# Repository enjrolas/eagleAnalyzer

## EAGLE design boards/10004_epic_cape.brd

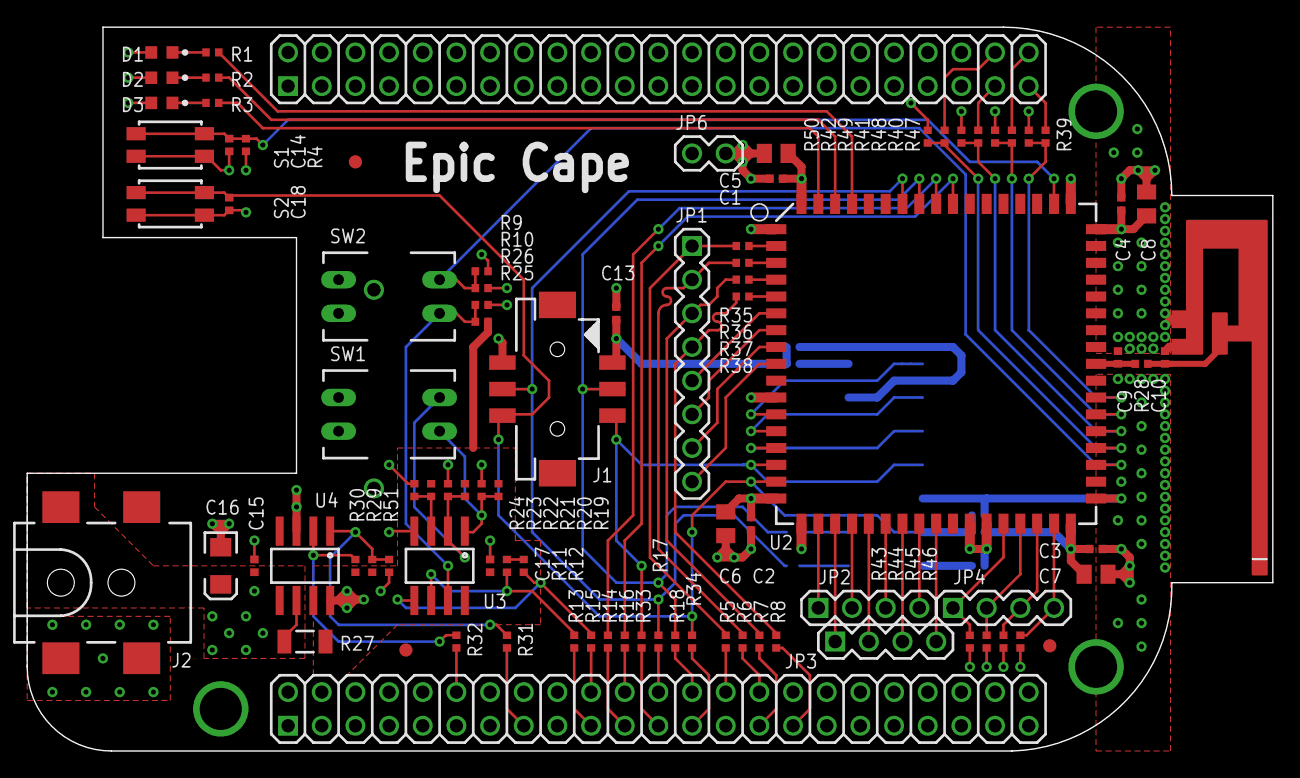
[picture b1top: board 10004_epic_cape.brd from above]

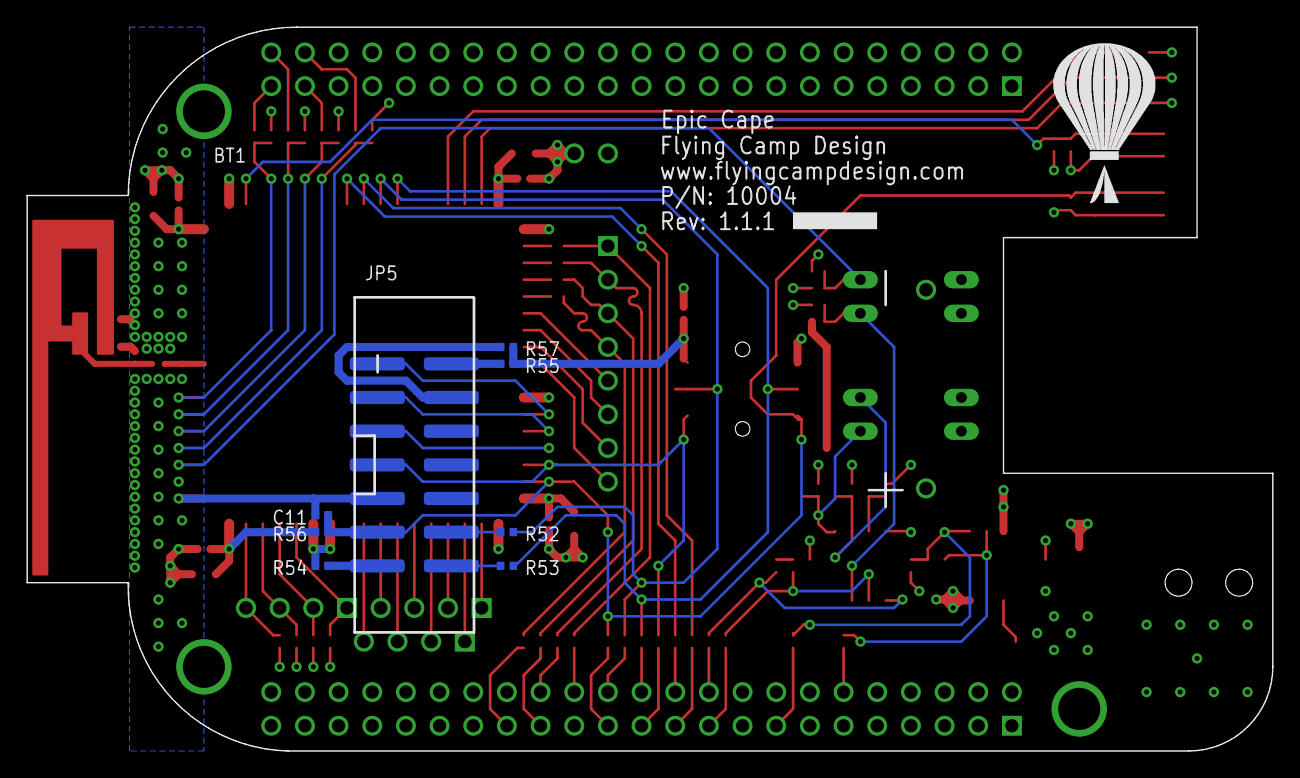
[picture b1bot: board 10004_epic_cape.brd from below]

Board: 4 copper layers, 94.0 x 54.6 mm, 99 parts (10 on the bottom side), 83 nets.

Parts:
ANT1: 2.4GHZ_INVERTED_F_ANTENNA
BT1: KEYSTONE_2462
C1, C2, C3, C4, C13, C14, C15, C17: 0.1u; CAPC1005
C5, C6, C7, C8: CAPC2012
C9, C10, C11, C18: CAPC1005
C16: 47u; EIA3216
D1: RED; LEDC1608
D2: GREEN; LEDC1608
D3: YELLOW; LEDC1608
J1: MSP430_BSL_HDR/SMD; HIROSE_DF11G-XXDP-2V
J2: 5.5x2.1mm Barrel; POWER_JACK_SMD
JP1: 1X08
JP2, JP3, JP4: 1X04
JP5: M07X2SHD_SMD; 2X7-SHROUDED_SMD
JP6: M02PTH; 1X02
R1, R2, R3: 470; RESC1005
R4, R29, R30, R43, R44, R45, R46, R47, R48, R49, R50, R51: 10K; RESC1005
R5, R6, R7, R8, R13, R14, R15, R16, R17, R18, R28, R31, R32, R33, R34, R35, R36, R37, R38, R39, R40, R41, R42, R52, R53, R54, R55, R57: 0; RESC1005
R9, R10, R19, R20, R21, R22, R23, R24, R25, R26: 100K; RESC1005
R11, R12: 5.6K; RESC1005
R27: 0; RESC3216
R56: RESC1005
S1, S2: PANASONIC_EVQP2
SW1, SW2: KAS1102ET; DIPSWITCH-02
U1: BEAGLEBONE_OUTLINE; BEAGLEBONE_SHIELD
U2: EPIC-CORE_A; EPIC_LCC68
U3: CAT24C256/SOIC-8; SOIC-8
U4: MIC2025/SOIC-8; SOIC-8
U$2: LOGO
U$3, U$4, U$5: FIDUCIAL1X2.5; FIDUCIAL-1X2.5

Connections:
3V3: BT1.+, C1.1, C2.1, C3.2, C4.2, C5.1, C6.1, C7.2, C8.2, C13.1, C15.1, C16.A, D1.A, D2.A, D3.A, J1.P$1, J2.VIN0, JP6.1, R4.2, R9.2, R27.1, R43.2, R44.2, R45.2, R46.2, R47.2, R48.2, R49.2, R50.2, R55.2, R56.2, R57.2, U2.P$17, U2.P$34, U2.P$51, U2.P$68, U4.6, U4.8
BB_GPIO1_16: R31.2, U1.61
BB_GPIO1_17: R33.2, U1.69
BB_GPIO1_28: R32.2, U1.58
BB_GPIO2_6: R39.2, U1.45
BB_GPIO2_7: R40.2, U1.46
BB_GPIO2_8: R41.2, U1.43
BB_GPIO2_9: R42.2, U1.44
BB_GPIO3_21: R34.2, U1.71
BB_I2C2_SCL: R11.1, R13.1, U3.6
BB_I2C2_SCL_ST: R13.2, U1.65
BB_I2C2_SDA: R12.1, R15.1, U3.5
BB_I2C2_SDA_ST: R15.2, U1.66
BB_SPI1_CS0: R5.2, U1.74
BB_SPI1_DI: R6.2, U1.76
BB_SPI1_DO: R7.2, U1.75
BB_SPI1_SCLK: R8.2, U1.77
BB_UART1_RXD: R18.2, U1.72
BB_UART1_TXD: R17.2, U1.70
BB_UART2_RXD: R16.2, U1.68
BB_UART2_TXD: R14.2, U1.67
CAPE_EEPROM_A0: R19.1, R20.2, SW1.1, U3.1
CAPE_EEPROM_A1: R21.1, R22.2, SW1.2, U3.2
CAPE_EEPROM_A2: R23.1, R24.2, U3.3
CAPE_EEPROM_WP: R25.1, R26.2, SW2.1, U3.7
EPIC_ADC0: JP2.1, U2.P$19
EPIC_ADC1: JP3.1, U2.P$20
EPIC_ADC2: JP2.2, U2.P$21
EPIC_ADC3: JP3.2, U2.P$22
EPIC_ADC4: JP2.3, U2.P$23
EPIC_ADC5: JP3.3, U2.P$24
EPIC_ADC6: JP2.4, U2.P$25
EPIC_ADC7: JP3.4, U2.P$26
EPIC_FLASH_WP: R9.1, R10.2, SW2.2, U2.P$37
EPIC_LED1: R1.2, U2.P$65
EPIC_LED2: R2.2, U2.P$66
EPIC_LED3: R3.2, U2.P$67
EPIC_MISO1: JP1.3, R7.1, R37.1
EPIC_MISO1_ST: R37.2, U2.P$4
EPIC_MOSI1: JP1.2, R6.1, R36.1
EPIC_MOSI1_ST: R36.2, U2.P$3
EPIC_P1.2: JP4.1, R43.1, U2.P$30
EPIC_P1.5: JP4.2, R44.1, U2.P$31
EPIC_P1.6: JP4.3, R45.1, U2.P$32
EPIC_P1.7: JP4.4, R46.1, U2.P$33
EPIC_P2.0: R42.1, R50.1, U2.P$38
EPIC_P2.1: R41.1, R49.1, U2.P$39
EPIC_P2.3: R40.1, R48.1, U2.P$40
EPIC_P2.6: R39.1, R47.1, U2.P$41
EPIC_P5.4: JP1.5, U2.P$6
EPIC_P5.5: JP1.6, U2.P$7
EPIC_P5.6: JP1.7, U2.P$8
EPIC_P5.7: JP1.8, U2.P$9
EPIC_RFOUT: C9.1, R28.1, U2.P$43
EPIC_RST/NMI: C11.1, C18.1, J1.P$6, JP5.11, R34.1, R56.1, S2.P$1, S2.P$3, U2.P$16
EPIC_SCLK1: JP1.4, R8.1, R38.1
EPIC_SCLK1_ST: R38.2, U2.P$5
EPIC_STE1: JP1.1, R5.1, R35.1
EPIC_STE1_ST: R35.2, U2.P$2
EPIC_TCK: J1.P$5, JP5.7, R33.1, U2.P$15
EPIC_TDI/TCLK: JP5.3, U2.P$13
EPIC_TDO/TDI: JP5.1, U2.P$12
EPIC_TMS: JP5.5, U2.P$14
EPIC_UART0RX: R14.1, U2.P$60
EPIC_UART0TX: R16.1, U2.P$59
EPIC_UART1RX: J1.P$4, R17.1, R53.2, U2.P$62
EPIC_UART1TX: J1.P$3, R18.1, R52.2, U2.P$61
EPIC_USER_INT: C14.1, R4.1, S1.P$1, S1.P$3, U2.P$53
FEED: ANT1.FEED, C10.1, R28.2
GND: BT1.-, C1.2, C2.2, C3.1, C4.1, C5.2, C6.2, C7.1, C8.1, C11.2, C13.2, C14.2, C15.2, C16.C, C17.2, C18.2, J1.P$2, J2.GND, J2.P$4, JP5.9, JP6.2, R10.1, R20.1, R22.1, R24.1, R26.1, R51.1, R54.1, S1.P$2, S1.P$4, S2.P$2, S2.P$4, SW1.3, SW1.4, SW2.3, SW2.4, U1.1, U1.2, U1.47, U1.48, U1.80, U1.89, U1.90, U1.91, U1.92, U2.P$1, U2.P$11, U2.P$18, U2.P$28, U2.P$29, U2.P$35, U2.P$52, U3.4, U4.3
unnamed: JP5.13, R54.2
unnamed: D1.C, R1.1
unnamed: D2.C, R2.1
unnamed: D3.C, R3.1
unnamed: JP5.12, R52.1
unnamed: JP5.14, R53.1
PWR_EN: R29.1, R31.1, R51.2, U4.1
PWR_FLG: R30.1, R32.1, U4.2
RFGND: ANT1.GND@1, ANT1.GND@2, C9.2, C10.2, U2.P$42, U2.P$44
VCCTARGET: JP5.4, R57.1
VCCTOOL: JP5.2, R55.1
VDD_3V3EXP: C17.1, R11.2, R12.2, R19.2, R21.2, R23.2, R25.2, R27.2, R29.2, R30.2, U1.49, U1.50, U3.8, U4.7
VDD_5V: U1.51, U1.52

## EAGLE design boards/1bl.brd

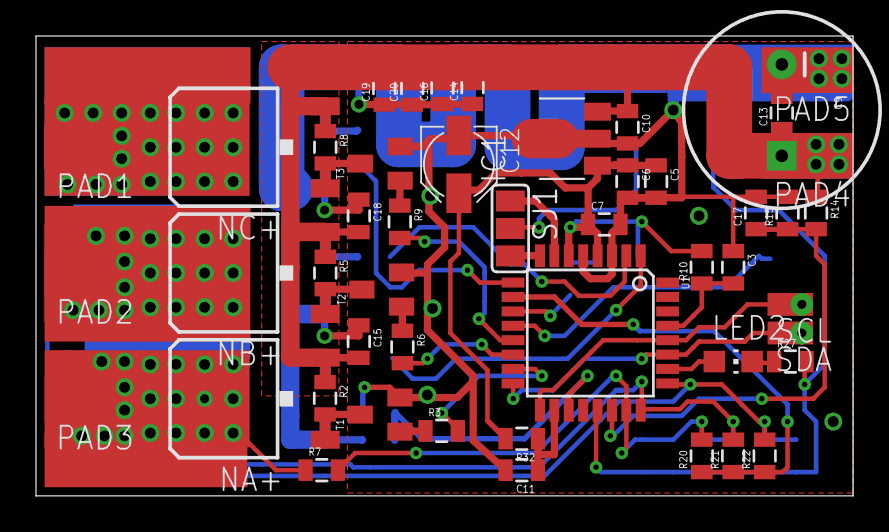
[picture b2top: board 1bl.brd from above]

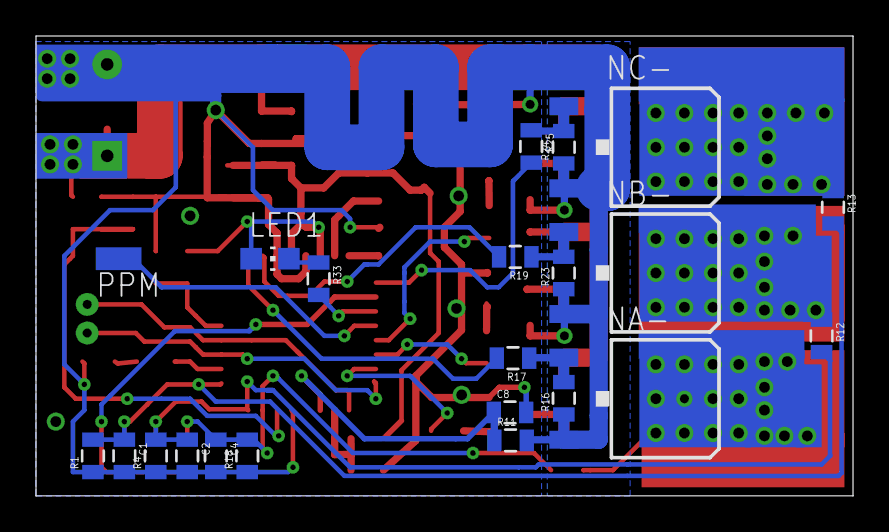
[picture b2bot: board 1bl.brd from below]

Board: 2 copper layers, 45.4 x 25.5 mm, 70 parts (22 on the bottom side), 39 nets.

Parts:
C1, C2, C3, C4, C5, C6, C7, C8, C10, C11, C13, C14, C17, C19, C20: 100n; 0805
C9: 330µF/25V; CPOL-RADIAL-1000UF-25V
C12: 10µF; PANASONIC_B
C15, C18: 0805
C16: 1µ; 0805
IC1: 78L05F; SOT89
LED1, LED2: CHIP-LED0805
NA+: IRFR5305 oder FDD6637; D-PAK_TO252AA
NA-: IRFR1205 oder IPD03N03LB oder IRLR7843; D-PAK_TO252AA
NB+: IRFR5305 oder FDD6637; D-PAK_TO252AA
NB-: IRFR1205 oder IPD03N03LB oder IRLR7843; D-PAK_TO252AA
NC+: IRFR5305 oder FDD6637; D-PAK_TO252AA
NC-: IRFR1205 oder IPD03N03LB oder IRLR7843; D-PAK_TO252AA
PAD1, PAD2, PAD3, PAD4, PAD5: SMD2,54-5,08
PPM: SMD1,27-2,54
R1, R4, R7, R12, R13, R18, R20, R21, R22: 4k7; 0805
R2, R5, R8: 470R; 0805
R3, R6, R9: 0R; 0805
R10: 10K; 0805
R11: 680R; 0805
R14, R16, R23, R24: 18k; 0805
R15: 1k; 0805
R17, R19, R25: 100R; 0805
R27, R33: 1K; 0805
R32: 10R; 0805
SCL: SMD1,27-2,54
SDA: SMD1,27-2,54
SJ1: SJ_2
T1, T2, T3: PDTC143; SOT23
U1: ATMEGA168; TQFP32-08

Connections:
+5V: C5.1, C6.1, C7.1, C12.+, IC1.1, LED1.A, R10.2, R32.2, U1.4, U1.6
ADR1: SJ1.1, U1.7
ADR2: SJ1.3, U1.8
GND: C1.2, C2.2, C3.1, C4.2, C5.2, C6.2, C7.2, C8.2, C9.2, C10.2, C11.2, C12.-, C13.2, C17.2, IC1.2, IC1.2@1, PAD5.1, R1.1, R4.1, R15.2, R18.1, R27.2, SJ1.2, T1.2, T2.2, T3.2, U1.3, U1.5, U1.21
GNDI: C14.1, C15.1, C16.1, C18.1, C19.1, C20.1, NA-.3, NB-.3, NC-.3, R11.2, R16.1, R23.1, R24.1
LED_GRN: R33.2, U1.11
LED_ROT: LED2.A, U1.26
MITTEL: R20.1, R21.1, R22.1, U1.10
unnamed: C11.1, R32.1, U1.18
unnamed: NC+.1, R8.2, T3.3
unnamed: NB+.1, R5.2, T2.3
unnamed: NA+.1, R2.2, T1.3
unnamed: LED1.C, R33.1
unnamed: LED2.C, R27.1
unnamed: NA-.1, R16.2, R17.1
unnamed: NB-.1, R19.1, R23.2
unnamed: NC-.1, R24.2, R25.1
unnamed: R3.1, T1.1
unnamed: R6.1, T2.1
unnamed: R9.1, T3.1
NULL_A: C4.1, R7.2, R18.2, R20.2, U1.23
NULL_B: C2.1, R4.2, R12.2, R21.2, U1.24
NULL_C: C1.1, R1.2, R13.2, R22.2, U1.25
PHASE_A: NA+.4, NA-.4, PAD3.1, R7.1
PHASE_B: NB+.4, NB-.4, PAD2.1, R12.1
PHASE_C: NC+.4, NC-.4, PAD1.1, R13.1
PPM: PPM.1, U1.12
RESET: C3.2, R10.1, U1.29
SCL: SCL.1, U1.17, U1.28
SDA: SDA.1, U1.16, U1.27
STEUER_A+: R3.2, U1.15
STEUER_A-: R17.2, U1.1
STEUER_B+: R6.2, U1.14
STEUER_B-: R19.2, U1.2
STEUER_C+: R9.2, U1.13
STEUER_C-: R25.2, U1.9
STROM: C8.1, R11.1, U1.19
VCC: C9.1, C10.1, C13.1, C14.2, C15.2, C16.2, C18.2, C19.2, C20.2, IC1.3, NA+.3, NB+.3, NC+.3, PAD4.1, R2.1, R5.1, R8.1, R14.1
V_BAT: C17.1, R14.2, R15.1, U1.22

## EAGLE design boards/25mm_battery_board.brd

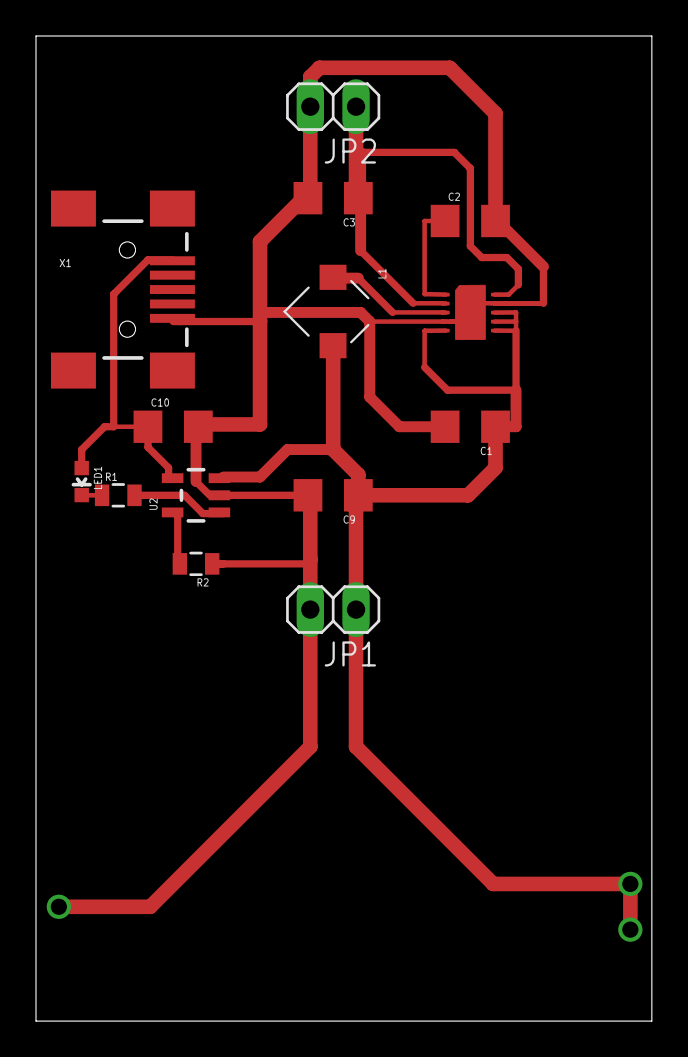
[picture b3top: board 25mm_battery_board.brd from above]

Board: 2 copper layers, 34.2 x 54.7 mm, 14 parts (0 on the bottom side), 9 nets.

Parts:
C1, C2, C3: 10uF; 1206
C9, C10: 4.7uF; 1206
JP1: BATT_CONN; 1X02
JP2: VOUT_HDR; 1X02
L1: 2.2uH; CDRH3D28
LED1: LED-0603
R1: 150; 0805
R2: 27k; 0805
U2: MCP73831; SOT23-5
U$1: TPS61200-WQFN; QFN-10
X1: USBSMD; USB-MINIB

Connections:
GND: C1.2, C2.2, C3.2, C9.2, C10.2, JP1.2, JP2.2, R2.1, U2.2, U$1.4, U$1.9, X1.GND
unnamed: R1.2, U2.1
unnamed: L1.1, U$1.3
unnamed: LED1.C, R1.1
unnamed: C2.1, U$1.1
unnamed: R2.2, U2.5
VBATT: C1.1, C9.1, JP1.1, L1.2, U2.3, U$1.5, U$1.6, U$1.7, U$1.8
VOUT: C3.1, JP2.1, U$1.2, U$1.10
VUSB: C10.1, LED1.A, U2.4, X1.VBUS

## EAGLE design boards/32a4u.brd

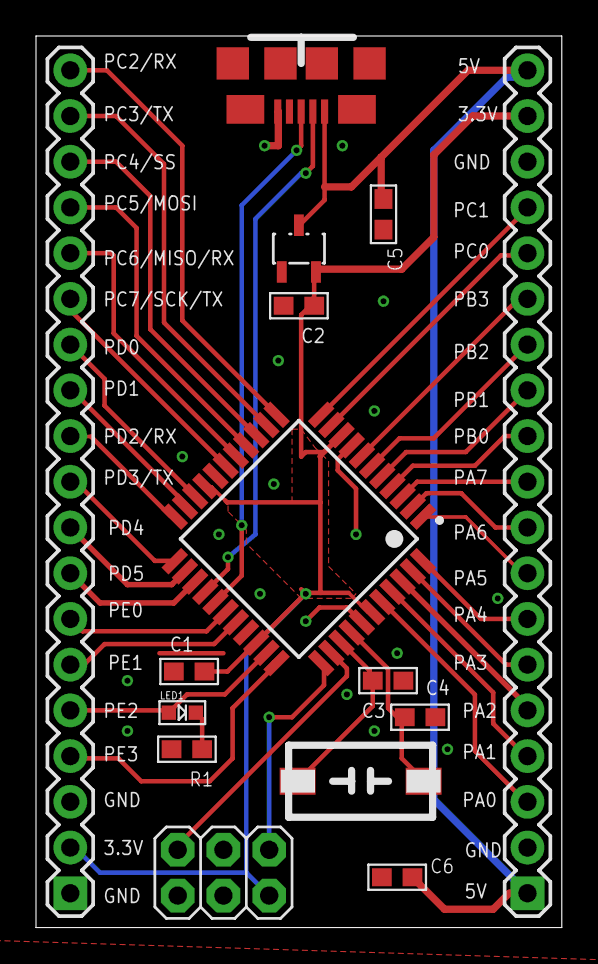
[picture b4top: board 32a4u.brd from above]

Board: 2 copper layers, 29.2 x 49.5 mm, 15 parts (0 on the bottom side), 40 nets.

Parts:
ATXMEGA32A4U: TQFP-44
C1, C2, C3, C4, C5, C6: 0603
CN1: USB-MICROB
JP1: 2X03
LED1: CHIPLED_0603
R1: 0603
U$2: MCP1700; SOT23-3
U$3, U$4: M19; 1X19
Y1: NX8045GB

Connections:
GND: ATXMEGA32A4U.8, ATXMEGA32A4U.18, ATXMEGA32A4U.30, ATXMEGA32A4U.38, C1.2, C2.2, C3.2, C4.2, C5.2, C6.1, CN1.P5, JP1.6, R1.2, U$2.GND, U$3.2, U$3.17, U$4.1, U$4.3
unnamed: LED1.C, R1.1
PA0: ATXMEGA32A4U.40, U$3.3
PA1: ATXMEGA32A4U.41, U$3.4
PA2: ATXMEGA32A4U.42, U$3.5
PA3: ATXMEGA32A4U.43, U$3.6
PA4: ATXMEGA32A4U.44, U$3.7
PA5: ATXMEGA32A4U.1, U$3.8
PA6: ATXMEGA32A4U.2, U$3.9
PA7: ATXMEGA32A4U.3, U$3.10
PB0: ATXMEGA32A4U.4, U$3.11
PB1: ATXMEGA32A4U.5, U$3.12
PB2: ATXMEGA32A4U.6, U$3.13
PB3: ATXMEGA32A4U.7, U$3.14
PC0: ATXMEGA32A4U.10, U$3.15
PC1: ATXMEGA32A4U.11, U$3.16
PC2: ATXMEGA32A4U.12, U$4.19
PC3: ATXMEGA32A4U.13, U$4.18
PC4: ATXMEGA32A4U.14, U$4.17
PC5: ATXMEGA32A4U.15, U$4.16
PC6: ATXMEGA32A4U.16, U$4.15
PC7: ATXMEGA32A4U.17, U$4.14
PD0: ATXMEGA32A4U.20, U$4.13
PD1: ATXMEGA32A4U.21, U$4.12
PD2: ATXMEGA32A4U.22, U$4.11
PD3: ATXMEGA32A4U.23, U$4.10
PD4: ATXMEGA32A4U.24, U$4.9
PD5: ATXMEGA32A4U.25, U$4.8
PDI-CLK: ATXMEGA32A4U.35, JP1.5
PDI-DATA: ATXMEGA32A4U.34, JP1.1
PE0: ATXMEGA32A4U.28, U$4.7
PE1: ATXMEGA32A4U.29, U$4.6
PE2: ATXMEGA32A4U.32, LED1.A, U$4.5
PE3: ATXMEGA32A4U.33, U$4.4
PR0: ATXMEGA32A4U.36, C3.1, Y1.P$2
PR1: ATXMEGA32A4U.37, C4.1, Y1.P$1
USB+: ATXMEGA32A4U.27, CN1.P3
USB-: ATXMEGA32A4U.26, CN1.P2
VCC: ATXMEGA32A4U.9, ATXMEGA32A4U.19, ATXMEGA32A4U.31, ATXMEGA32A4U.39, C1.1, C2.1, JP1.2, U$2.VOUT, U$3.18, U$4.2
VUSB: C5.1, C6.2, CN1.P1, U$2.VIN, U$3.1, U$3.19

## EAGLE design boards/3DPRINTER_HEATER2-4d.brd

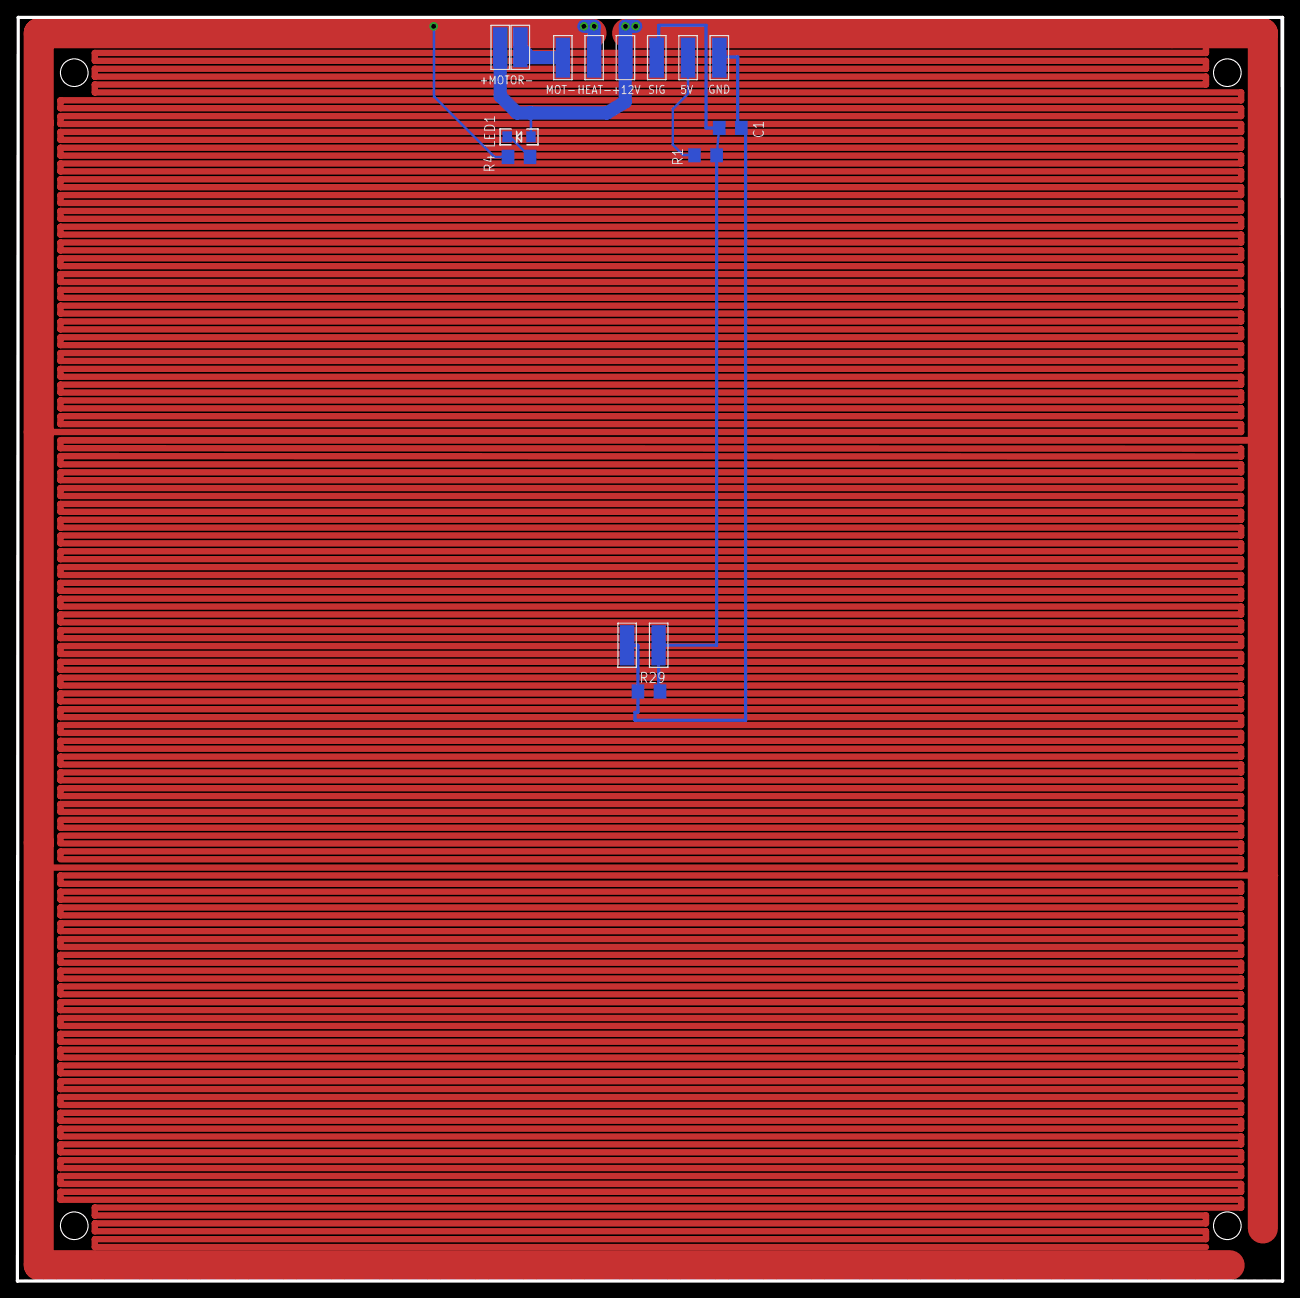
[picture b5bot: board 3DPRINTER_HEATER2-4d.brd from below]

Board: 2 copper layers, 160.2 x 160.0 mm, 15 parts (15 on the bottom side), 6 nets.

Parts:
+12V: WIREPADSMD5-1,8; 5-1,8
C1: C1206
GND-PAD1, GND-PAD7: WIREPADSMD5-1,8; 5-1,8
HEATER-: WIREPADSMD5-1,8; 5-1,8
LED1: LED-1206
MOTOR+: WIREPADSMD5-1,8; 5-1,8
MOTOR-: WIREPADSMD5-1,8; 5-1,8
MPOWER-: WIREPADSMD5-1,8; 5-1,8
R1, R4, R29: 1206
SIG-PAD1, SIG-PAD5: WIREPADSMD5-1,8; 5-1,8
VCC-PAD6: WIREPADSMD5-1,8; 5-1,8

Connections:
unnamed: LED1.C, R4.2
unnamed: C1.2, GND-PAD1.1, GND-PAD7.1, R29.1
unnamed: C1.1, R1.1, R29.2, SIG-PAD1.1, SIG-PAD5.1
unnamed: MOTOR-.1, MPOWER-.1
unnamed: R1.2, VCC-PAD6.1
unnamed: +12V.1, LED1.A, MOTOR+.1

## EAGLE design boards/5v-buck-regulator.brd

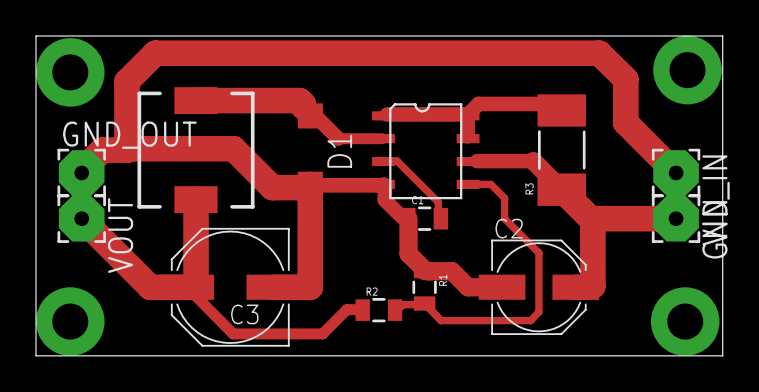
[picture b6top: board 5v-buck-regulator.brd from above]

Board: 2 copper layers, 38.2 x 17.8 mm, 13 parts (0 on the bottom side), 7 nets.

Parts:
C1: 470pF; 0805
C2: 100uF; PANASONIC_C
C3: 470uF; PANASONIC_D
D1: 1N5819; SOD123
GND_IN: 2,54/0,8
GND_OUT: 2,54/0,8
L1: B82462G
R1: 1k8; 0805
R2: 5k6; 0805
R3: 20mOhm; R2010
U1: MC33063AP; SOIC-8
VIN: 2,54/0,8
VOUT: 2,54/0,8

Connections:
GND: C1.1, C2.-, C3.-, D1.A, GND_IN.1, GND_OUT.1, R1.1, U1.4
unnamed: C1.2, U1.3
unnamed: R3.2, U1.1, U1.7, U1.8
unnamed: D1.C, L1.P$1, U1.2
unnamed: R1.2, R2.2, U1.5
VIN: C2.+, R3.1, U1.6, VIN.1
VOUT: C3.+, L1.P$2, R2.1, VOUT.1

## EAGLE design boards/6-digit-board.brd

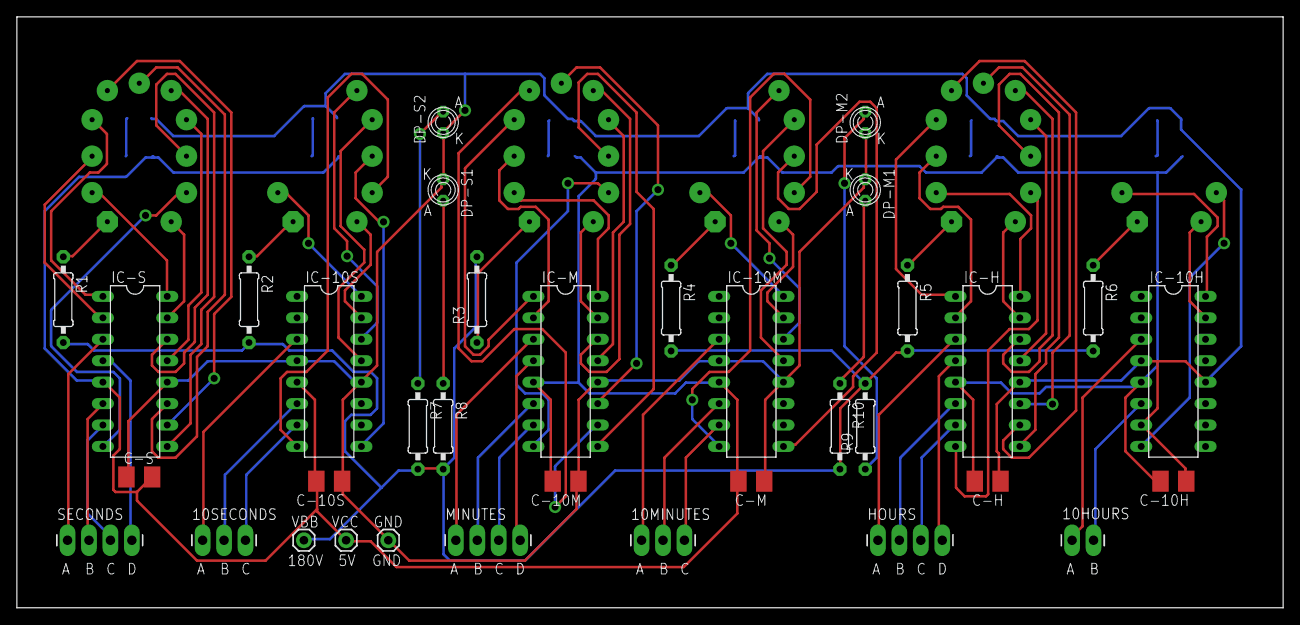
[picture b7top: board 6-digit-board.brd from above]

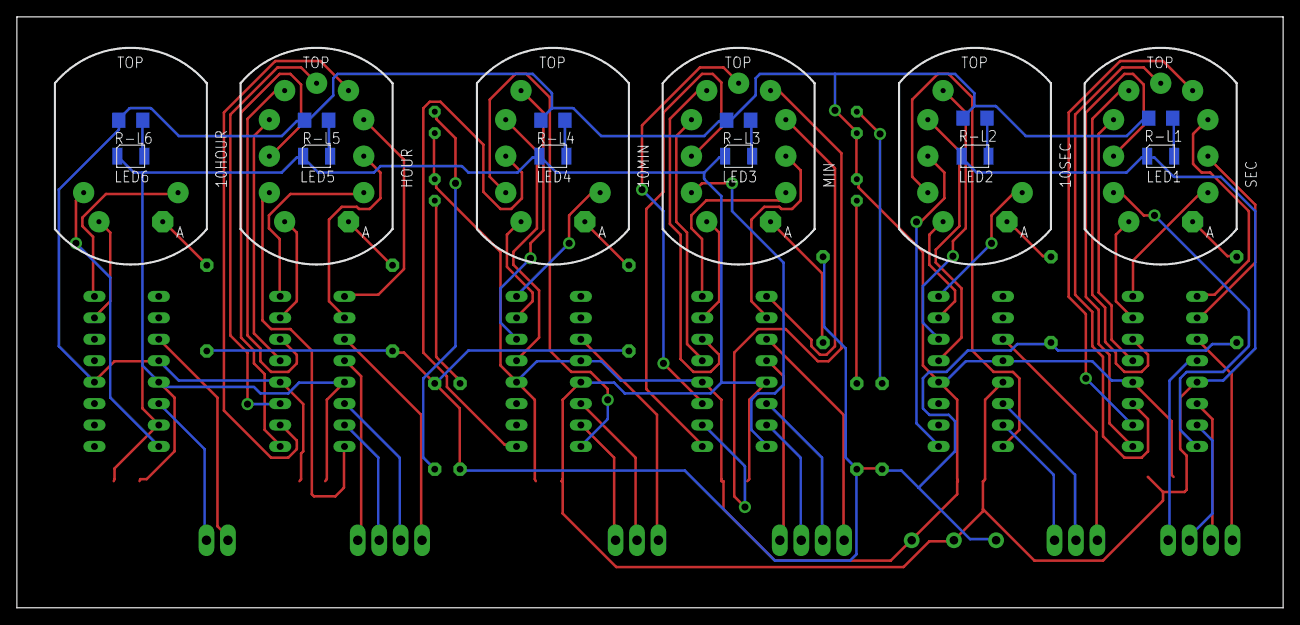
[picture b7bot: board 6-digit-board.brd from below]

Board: 2 copper layers, 150.0 x 70.0 mm, 53 parts (18 on the bottom side), 84 nets.

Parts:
10HOUR: IN-12_2DIGIT
10HOURS: 1X02_LONGPADS
10MIN, 10SEC: IN-12_6DIGIT
10MINUTES, 10SECONDS: 1X03_LONGPADS
C-10H, C-10M, C-10S: 10uF; B/3528-21R
C-H: 10uF; B/3528-21R
C-M: 10uF; B/3528-21R
C-S: 10uF; B/3528-21R
DP-M1, DP-M2: INS-1
DP-S1, DP-S2: INS-1
GND: 1X01
HOUR: IN-12A-NO_DP; IN-12_NO-DP
HOURS: 1X04_LONGPADS
IC-10H, IC-10M, IC-10S: 74141N; DIL16
IC-H: 74141N; DIL16
IC-M: 74141N; DIL16
IC-S: 74141N; DIL16
LED1, LED2, LED3, LED4, LED5, LED6: LED1210
MIN: IN-12A-NO_DP; IN-12_NO-DP
MINUTES: 1X04_LONGPADS
R1, R2, R3, R4, R5, R6: 22K; 0207/10
R7, R8, R9, R10: 62K; 0207/10
R-L1, R-L2, R-L3, R-L4, R-L5, R-L6: R1206
SEC: IN-12A-NO_DP; IN-12_NO-DP
SECONDS: 1X04_LONGPADS
VBB: 1X01
VCC: 1X01

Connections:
GND: C-10H.-, C-10M.-, C-10S.-, C-H.-, C-M.-, C-S.-, DP-M1.K, DP-M2.K, DP-S1.K, DP-S2.K, GND.1, IC-10H.4, IC-10H.7, IC-10H.12, IC-10M.4, IC-10M.12, IC-10S.4, IC-10S.12, IC-H.12, IC-M.12, IC-S.12, R-L1.1, R-L2.1, R-L3.1, R-L4.1, R-L5.1, R-L6.1
unnamed: 10HOUR.A, R6.1
unnamed: HOUR.A, R5.1
unnamed: 10MIN.A, R4.1
unnamed: MIN.A, R3.1
unnamed: 10SEC.A, R2.1
unnamed: R1.1, SEC.A
unnamed: HOURS.1, IC-H.3
unnamed: HOURS.2, IC-H.6
unnamed: DP-M1.A, R10.1
unnamed: DP-M2.A, R9.1
unnamed: DP-S1.A, R8.1
unnamed: DP-S2.A, R7.1
unnamed: HOUR.0, IC-H.16
unnamed: HOUR.1, IC-H.15
unnamed: HOUR.2, IC-H.8
unnamed: HOUR.3, IC-H.9
unnamed: HOUR.4, IC-H.13
unnamed: HOUR.5, IC-H.14
unnamed: HOUR.6, IC-H.11
unnamed: HOUR.7, IC-H.10
unnamed: HOUR.8, IC-H.1
unnamed: HOUR.9, IC-H.2
unnamed: 10HOUR.1, IC-10H.15
unnamed: 10HOUR.0, IC-10H.16
unnamed: 10HOUR.2, IC-10H.8
unnamed: 10MIN.0, IC-10M.16
unnamed: 10MIN.1, IC-10M.15
unnamed: 10MIN.2, IC-10M.8
unnamed: 10MIN.3, IC-10M.9
unnamed: 10MIN.4, IC-10M.13
unnamed: 10MIN.5, IC-10M.14
unnamed: IC-M.16, MIN.0
unnamed: IC-M.15, MIN.1
unnamed: IC-M.8, MIN.2
unnamed: IC-M.9, MIN.3
unnamed: IC-M.13, MIN.4
unnamed: IC-M.14, MIN.5
unnamed: IC-M.11, MIN.6
unnamed: IC-M.10, MIN.7
unnamed: IC-M.1, MIN.8
unnamed: IC-M.2, MIN.9
unnamed: 10SEC.0, IC-10S.16
unnamed: 10SEC.1, IC-10S.15
unnamed: 10SEC.2, IC-10S.8
unnamed: 10SEC.3, IC-10S.9
unnamed: 10SEC.4, IC-10S.13
unnamed: 10SEC.5, IC-10S.14
unnamed: IC-S.16, SEC.0
unnamed: IC-S.15, SEC.1
unnamed: IC-S.8, SEC.2
unnamed: IC-S.9, SEC.3
unnamed: IC-S.13, SEC.4
unnamed: IC-S.14, SEC.5
unnamed: IC-S.11, SEC.6
unnamed: IC-S.10, SEC.7
unnamed: IC-S.1, SEC.8
unnamed: IC-S.2, SEC.9
unnamed: HOURS.3, IC-H.7
unnamed: HOURS.4, IC-H.4
unnamed: IC-S.3, SECONDS.1
unnamed: IC-S.6, SECONDS.2
unnamed: IC-S.7, SECONDS.3
unnamed: IC-S.4, SECONDS.4
unnamed: IC-M.3, MINUTES.1
unnamed: IC-M.6, MINUTES.2
unnamed: IC-M.7, MINUTES.3
unnamed: IC-M.4, MINUTES.4
unnamed: 10SECONDS.1, IC-10S.3
unnamed: 10SECONDS.2, IC-10S.6
unnamed: 10SECONDS.3, IC-10S.7
unnamed: 10MINUTES.1, IC-10M.3
unnamed: 10MINUTES.2, IC-10M.6
unnamed: 10MINUTES.3, IC-10M.7
unnamed: 10HOURS.1, IC-10H.3
unnamed: 10HOURS.2, IC-10H.6
unnamed: LED1.A, R-L1.2
unnamed: LED2.A, R-L2.2
unnamed: LED3.A, R-L3.2
unnamed: LED4.A, R-L4.2
unnamed: LED5.A, R-L5.2
unnamed: LED6.A, R-L6.2
VBB: R1.2, R2.2, R3.2, R4.2, R5.2, R6.2, R7.2, R8.2, R9.2, R10.2, VBB.1
VCC: C-10H.+, C-10M.+, C-10S.+, C-H.+, C-M.+, C-S.+, IC-10H.5, IC-10M.5, IC-10S.5, IC-H.5, IC-M.5, IC-S.5, LED1.C, LED2.C, LED3.C, LED4.C, LED5.C, LED6.C, VCC.1

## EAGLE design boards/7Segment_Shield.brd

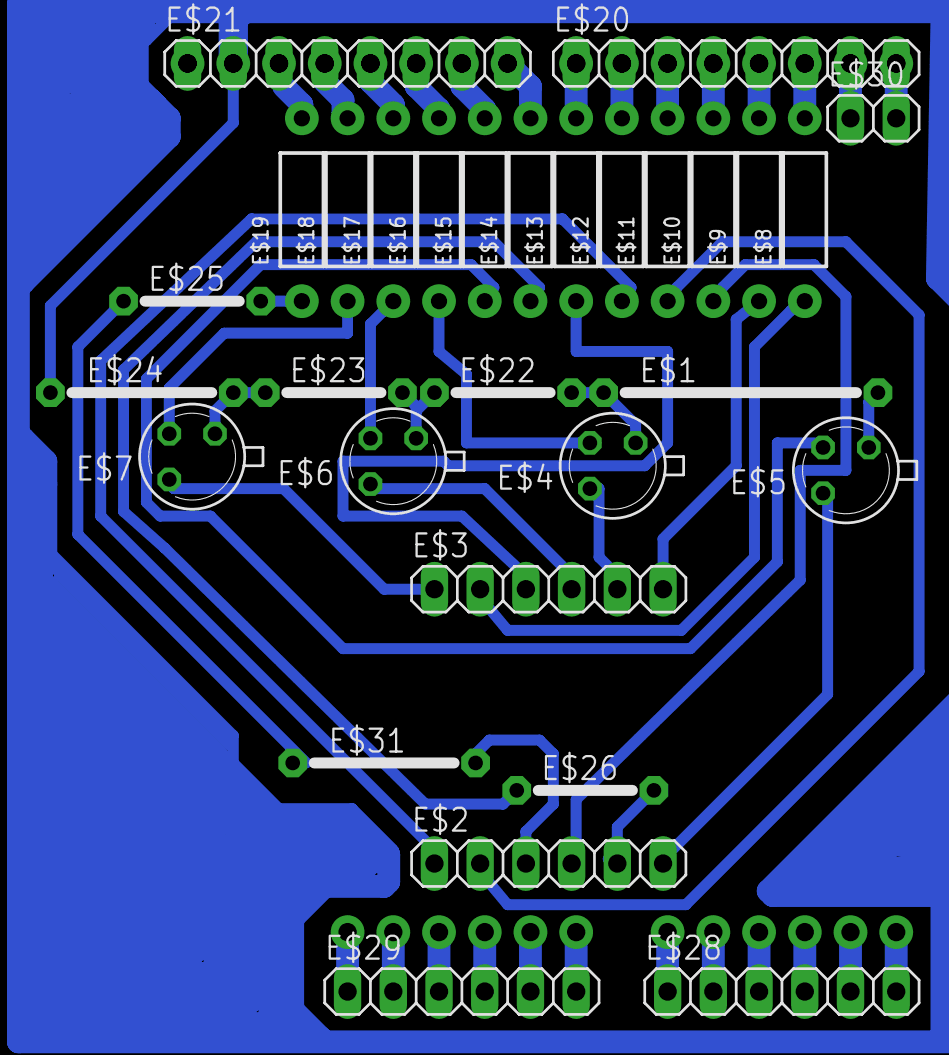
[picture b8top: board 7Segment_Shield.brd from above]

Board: 2 copper layers, 31 parts (0 on the bottom side), 29 nets.

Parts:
E$1: 15
E$2, E$3, E$28, E$29: 1X06
E$4, E$5, E$6, E$7: TO18A
E$8, E$9, E$10, E$11, E$12, E$13, E$14, E$15, E$16, E$17, E$18, E$19: AXIAL-0.4
E$20, E$21: 1X08
E$22, E$23, E$25, E$26: 07
E$24, E$31: 10
E$27: DUEMILANOVE_VIAS
E$30: 1X02

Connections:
S$12: E$7.B, E$18.P$1
S$13: E$6.B, E$17.P$1
S$14: E$4.B, E$16.P$1
S$15: E$5.B, E$15.P$1
S$16: E$7.E, E$23.1, E$24.2
S$17: E$3.1, E$7.C
S$18: E$3.4, E$6.C
S$19: E$3.5, E$4.C
S$20: E$3.2, E$8.P$1
S$21: E$3.6, E$9.P$1
S$22: E$2.4, E$10.P$1
S$23: E$2.2, E$11.P$1
S$24: E$3.3, E$13.P$1
S$25: E$2.6, E$5.C
S$26: E$14.P$1, E$26.1
S$27: E$6.E, E$22.1, E$23.2
S$28: E$1.1, E$4.E
S$29: E$19.P$1, E$25.2
S$30: E$1.2, E$5.E
S$31: E$2.1, E$12.P$1
S$34: E$21.2, E$24.1
S$37: E$27.3.3V, E$29.2
S$39: E$27.GND@0, E$29.4
S$41: E$27.VIN, E$29.6
S$42: E$27.A0, E$28.1
S$43: E$27.A1, E$28.2
S$44: E$27.A2, E$28.3
S$49: E$20.8, E$30.2
S$52: E$2.3, E$31.2

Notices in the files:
boards/32a4u.brd:
CC-By-SA
parts and their libraries:
SparkFun-Connectors: Licensing: CC v3.0 Share-Alike You are welcome to use this library for commercial purposes.
